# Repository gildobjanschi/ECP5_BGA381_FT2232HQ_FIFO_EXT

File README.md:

# Extension board for ECP5_BGA381_FT2232HQ_FIFO
This is an extension board for the [ECP5_BGA381_FT2232HQ_FIFO](https://github.com/gildobjanschi/ECP5_BGA381_FT2232HQ_FIFO) board. It is used to validate the main board design and to provide audio output connectors for I2S (HDMI) and SPDIF (Coaxial).

## Software
The bringup software that supports this board is located in the main board [ECP5_BGA381_FT2232HQ_FIFO](https://github.com/gildobjanschi/ECP5_BGA381_FT2232HQ_FIFO/tree/main/hdl_loopback) project. The [host software](https://github.com/gildobjanschi/ECP5_BGA381_FT2232HQ_FIFO/tree/main/host_loopback) is a simple application for testing the FIFO interface.

## Project Status
The board has been submitted to manufacturing to PCBWay.

[Schematic PDF](https://github.com/gildobjanschi/ECP5_BGA381_FT2232HQ_FIFO_EXT/blob/main/kicad/ECP5_Ext.pdf)

## How To setup KiCAD
Checkout the KiCAD project and open it. In the Configure Paths dialog add: Name: ECP5_BGA381_FT2232HQ_FIFO_EXT and Path: "The full path to the GitHub directory"/GitHub/ECP5_BGA381_FT2232HQ_FIFO_EXT

In the Manage Symbol Libraries click the Project Specific Libraries tab and add: Name: ECP5_BGA381_FT2232HQ_FIFO_EXT and Library Path: ${ECP5_BGA381_FT2232HQ_FIFO_EXT}/symbols/Symbols.kicad_sym

In the Manage Footprint Libraries click the Project Specific Libraries tab and add: Name: ECP5_BGA381_FT2232HQ_FIFO_EXT and Library Path: ${ECP5_BGA381_FT2232HQ_FIFO_EXT}/footprints/Footprints.pretty

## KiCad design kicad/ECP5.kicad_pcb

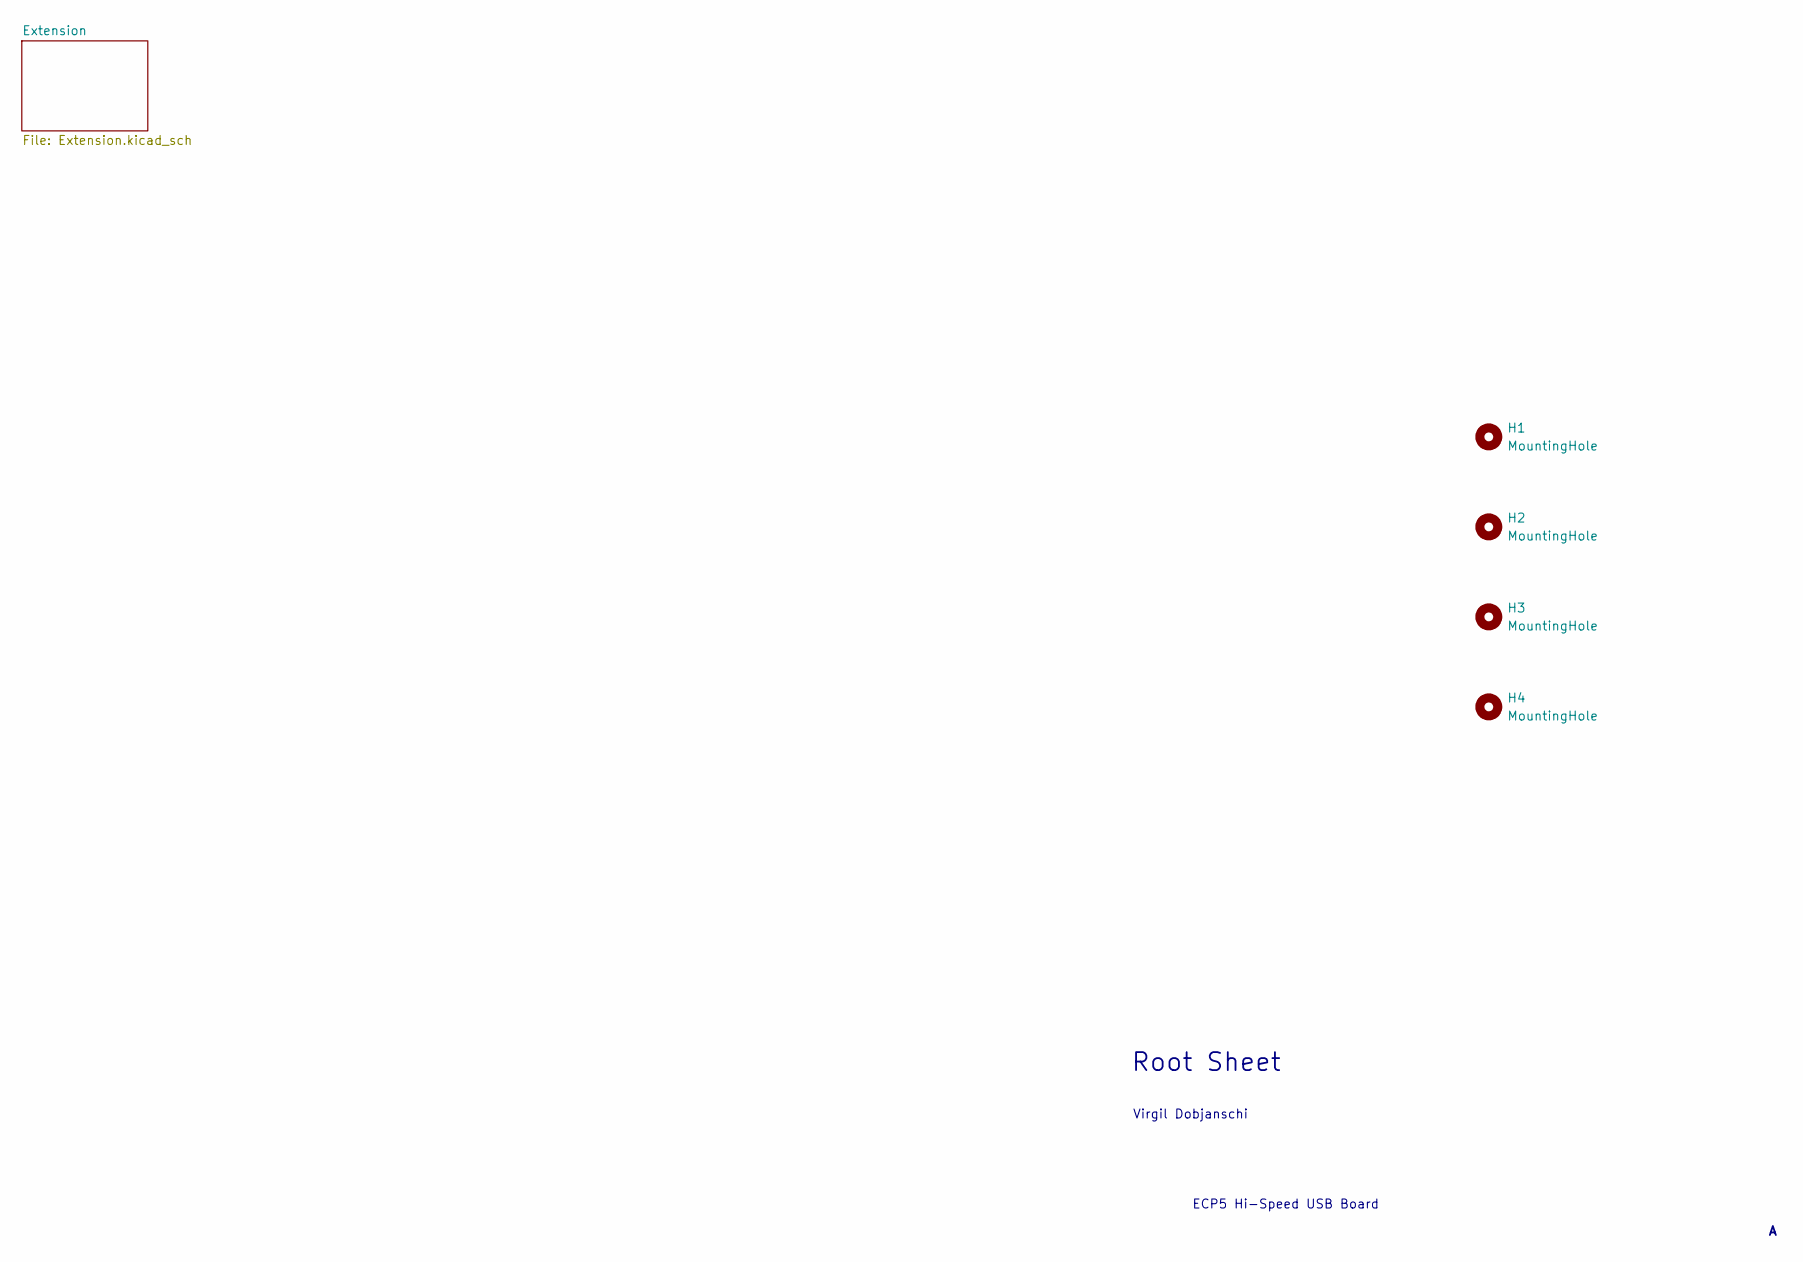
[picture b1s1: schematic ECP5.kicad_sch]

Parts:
H1, H2, H3, H4: MountingHole; MountingHole_3.2mm_M3

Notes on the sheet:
ECP5 Hi-Speed USB Board
Root Sheet
Virgil Dobjanschi

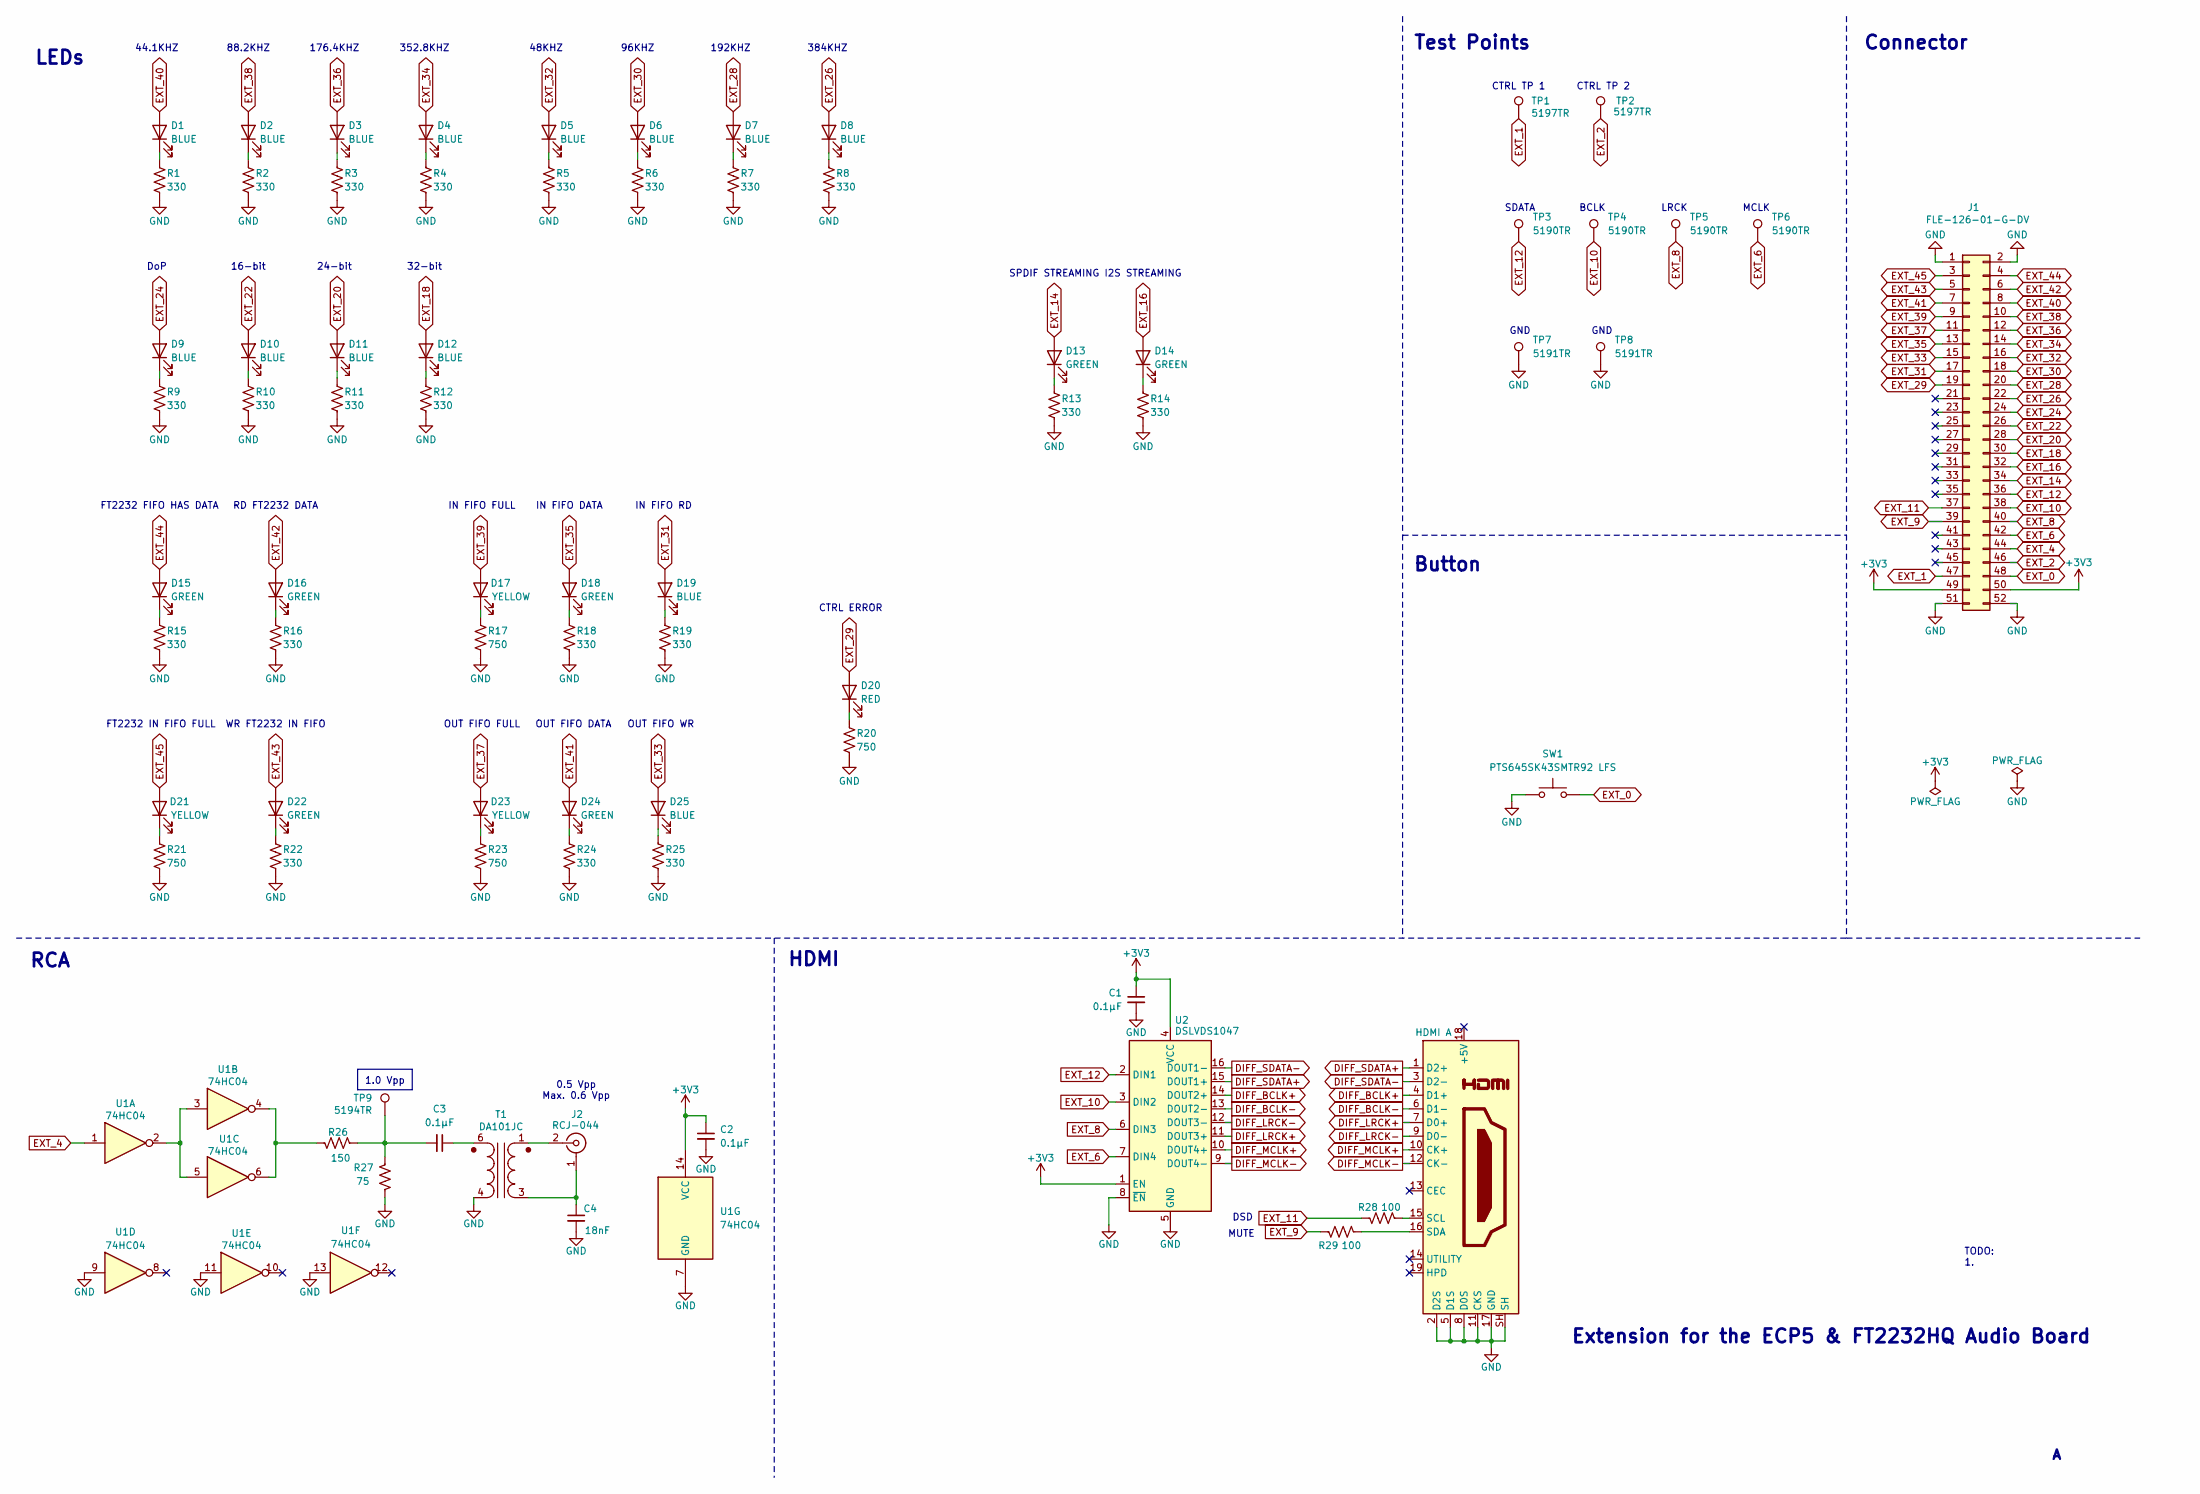
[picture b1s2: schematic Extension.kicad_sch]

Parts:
C1, C2, C3: 0.1µF; C_0603_1608Metric; MPN CL10B104KB8NNNC
C4: 18nF; C_0603_1608Metric; MPN CC0603KRX7R9BB183
D1, D2, D3, D4, D5, D6, D7, D8, D9, D10, D11, D12, D19, D25: BLUE; LED_0603_1608Metric; MPN APT1608LVBC/D
D13, D14, D15, D16, D18, D22, D24: GREEN; LED_0603_1608Metric; MPN APT1608LZGCK
D17, D21, D23: YELLOW; LED_0603_1608Metric; MPN APT1608LSYCK/J3-PRV
D20: RED; LED_0603_1608Metric; MPN APT1608LSECK/J3-PRV
J1: FLE-126-01-G-DV; SAMTEC_FLE-126-01-G-DV; MPN FLE-126-01-G-DV
J2: RCJ-044; CUI_RCJ-042; MPN RCJ-044
J3: HDMI A; AMPHENOL_10029449-001RLF; MPN 10029449-001RLF
R1, R2, R3, R4, R5, R6, R7, R8, R9, R10, R11, R12, R13, R14, R15, R16, R18, R19, R22, R24, R25: 330; R_0603_1608Metric; MPN ERJ-3EKF3300V
R17, R20, R21, R23: 750; R_0603_1608Metric; MPN ERJ-3EKF7500V
R26: 150; R_0603_1608Metric; MPN ERJ-3EKF1500V
R27: 75; R_0603_1608Metric; MPN ERJ-3EKF75R0V
R28, R29: 100; R_0603_1608Metric; MPN ERJ-3EKF1000V
SW1: PTS645SK43SMTR92 LFS; SW_SPST_PTS645; MPN PTS645SK43SMTR92 LFS
T1: DA101JC; DA101J_MUR; MPN DA101JC
TP1, TP2: 5197TR; KEYSTONE_5197TR; MPN 5197TR
TP3, TP4, TP5, TP6: 5190TR; KEYSTONE_5197TR; MPN 5190TR
TP7, TP8: 5191TR; KEYSTONE_5197TR; MPN 5191TR
TP9: 5194TR; KEYSTONE_5197TR; MPN 5194TR
U1: 74HC04; TSSOP-14_4.4x5mm_P0.65mm; MPN SN74HC04PWR
U2: DSLVDS1047; TSSOP-16-1EP_4.4x5mm_P0.65mm; MPN DSLVDS1047PWR

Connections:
+3V3: C1.1, C2.1, J1.49, J1.50, U1.14 (VCC), U2.1 (EN), U2.4 (VCC)
DIFF_BCLK+: J3.4 (D1+), U2.14 (DOUT2+)
DIFF_BCLK-: J3.6 (D1-), U2.13 (DOUT2-)
DIFF_LRCK+: J3.7 (D0+), U2.11 (DOUT3+)
DIFF_LRCK-: J3.9 (D0-), U2.12 (DOUT3-)
DIFF_MCLK+: J3.10 (CK+), U2.10 (DOUT4+)
DIFF_MCLK-: J3.12 (CK-), U2.9 (DOUT4-)
DIFF_SDATA+: J3.1 (D2+), U2.15 (DOUT1+)
DIFF_SDATA-: J3.3 (D2-), U2.16 (DOUT1-)
EXT_0: J1.48, SW1.2
EXT_1: J1.47, TP1.1
EXT_2: J1.46, TP2.1
EXT_4: J1.44, U1.1
EXT_6: J1.42, TP6.1, U2.7 (DIN4)
EXT_8: J1.40, TP5.1, U2.6 (DIN3)
EXT_9: J1.39, R29.2
EXT_10: J1.38, TP4.1, U2.3 (DIN2)
EXT_11: J1.37, R28.2
EXT_12: J1.36, TP3.1, U2.2 (DIN1)
EXT_14: D13.2 (A), J1.34
EXT_16: D14.2 (A), J1.32
EXT_18: D12.2 (A), J1.30
EXT_20: D11.2 (A), J1.28
EXT_22: D10.2 (A), J1.26
EXT_24: D9.2 (A), J1.24
EXT_26: D8.2 (A), J1.22
EXT_28: D7.2 (A), J1.20
EXT_29: D20.2 (A), J1.19
EXT_30: D6.2 (A), J1.18
EXT_31: D19.2 (A), J1.17
EXT_32: D5.2 (A), J1.16
EXT_33: D25.2 (A), J1.15
EXT_34: D4.2 (A), J1.14
EXT_35: D18.2 (A), J1.13
EXT_36: D3.2 (A), J1.12
EXT_37: D23.2 (A), J1.11
EXT_38: D2.2 (A), J1.10
EXT_39: D17.2 (A), J1.9
EXT_40: D1.2 (A), J1.8
EXT_41: D24.2 (A), J1.7
EXT_42: D16.2 (A), J1.6
EXT_43: D22.2 (A), J1.5
EXT_44: D15.2 (A), J1.4
EXT_45: D21.2 (A), J1.3
GND: C1.2, C2.2, C4.2, J1.1, J1.2, J1.51, J1.52, J3.2 (D2S), J3.5 (D1S), J3.8 (D0S), J3.11 (CKS), J3.17 (GND), J3.SH, R1.2, R2.2, R3.2, R4.2, R5.2, R6.2, R7.2, R8.2, R9.2, R10.2, R11.2, R12.2, R13.2, R14.2, R15.2, R16.2, R17.2, R18.2, R19.2, R20.2, R21.2, R22.2, R23.2, R24.2, R25.2, R27.2, SW1.1, T1.4 (SA), TP7.1, TP8.1, U1.7 (GND), U1.9, U1.11, U1.13, U2.5 (GND), U2.8 (~EN)
unnamed: C3.2, R26.1, R27.1, TP9.1
unnamed: D1.1 (K), R1.1
unnamed: D2.1 (K), R2.1
unnamed: D3.1 (K), R3.1
unnamed: D4.1 (K), R4.1
unnamed: D5.1 (K), R5.1
unnamed: D6.1 (K), R6.1
unnamed: D7.1 (K), R7.1
unnamed: D8.1 (K), R8.1
unnamed: D9.1 (K), R9.1
unnamed: D10.1 (K), R10.1
unnamed: D11.1 (K), R11.1
unnamed: D12.1 (K), R12.1
unnamed: D13.1 (K), R13.1
unnamed: D14.1 (K), R14.1
unnamed: D15.1 (K), R15.1
unnamed: D16.1 (K), R16.1
unnamed: D17.1 (K), R17.1
unnamed: D18.1 (K), R18.1
unnamed: D19.1 (K), R19.1
unnamed: D20.1 (K), R20.1
unnamed: D21.1 (K), R21.1
unnamed: D22.1 (K), R22.1
unnamed: D23.1 (K), R23.1
unnamed: D24.1 (K), R24.1
unnamed: D25.1 (K), R25.1
unnamed: C4.1, J2.1 (Ext), T1.3 (AB)
unnamed: J2.2 (In), T1.1 (AA)
unnamed: J3.15 (SCL), R28.1
unnamed: J3.16 (SDA), R29.1
unnamed: R26.2, U1.4, U1.6
unnamed: C3.1, T1.6 (SB)
unnamed: U1.2, U1.3, U1.5

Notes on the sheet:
24-bit
RCA
48KHZ
HDMI
IN FIFO DATA
SDATA
BCLK
DSD
192KHZ
FT2232 FIFO HAS DATA
CTRL TP 2
TODO: 1.
352.8KHZ
CTRL TP 1
Connector
RD FT2232 DATA
Button
IN FIFO RD
Test Points
GND
1.0 Vpp
OUT FIFO DATA
OUT FIFO WR
OUT FIFO FULL
44.1KHZ
176.4KHZ
96KHZ
FT2232 IN FIFO FULL
0.5 Vpp Max. 0.6 Vpp
CTRL ERROR
MCLK
Extension for the ECP5 & FT2232HQ Audio Board
SPDIF STREAMING
16-bit
WR FT2232 IN FIFO
LRCK
32-bit
384KHZ
I2S STREAMING
88.2KHZ

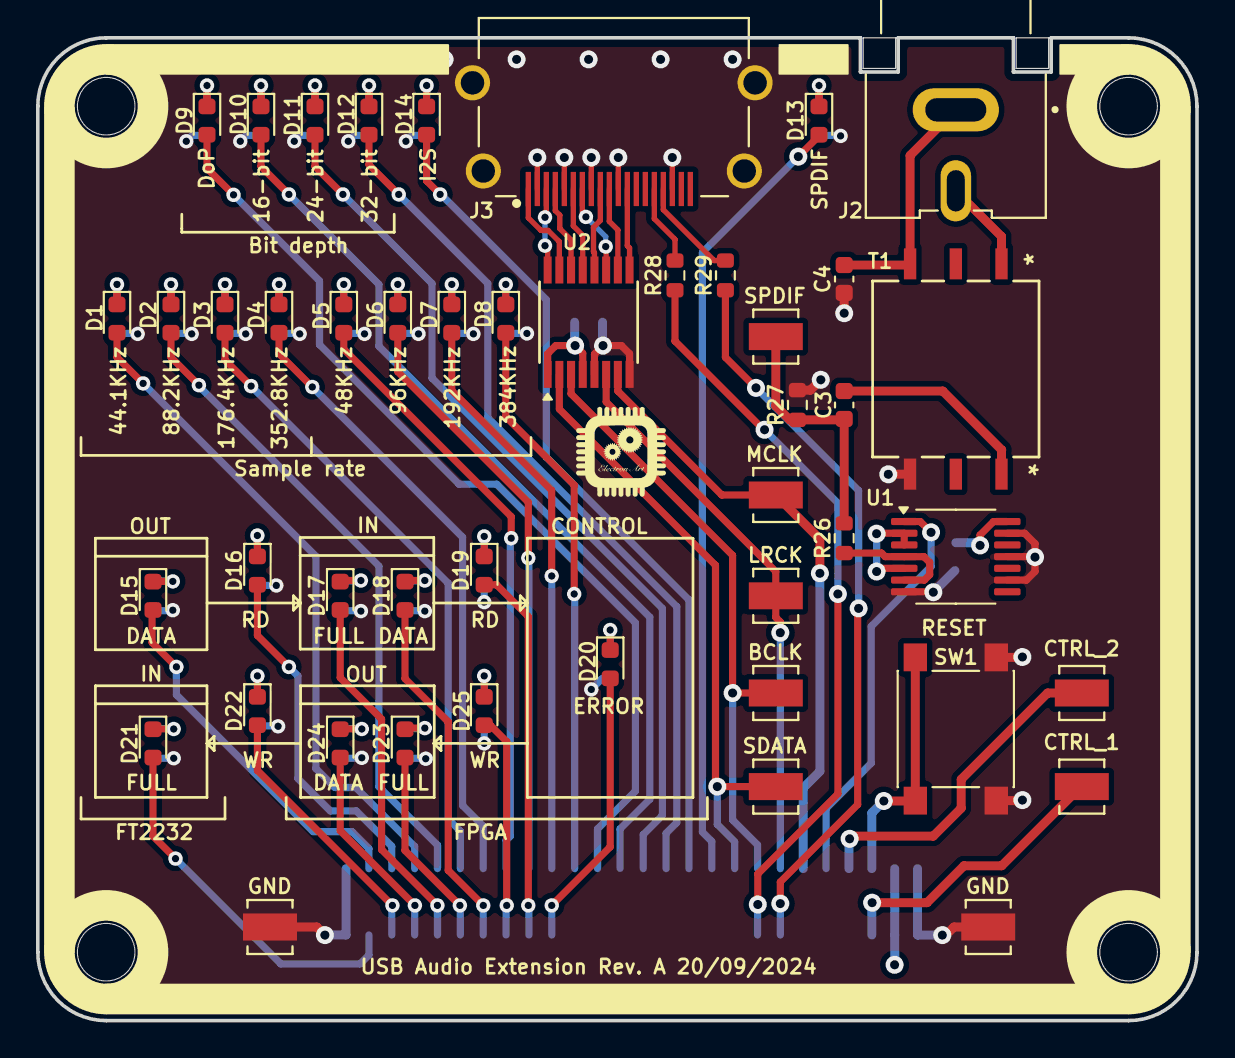
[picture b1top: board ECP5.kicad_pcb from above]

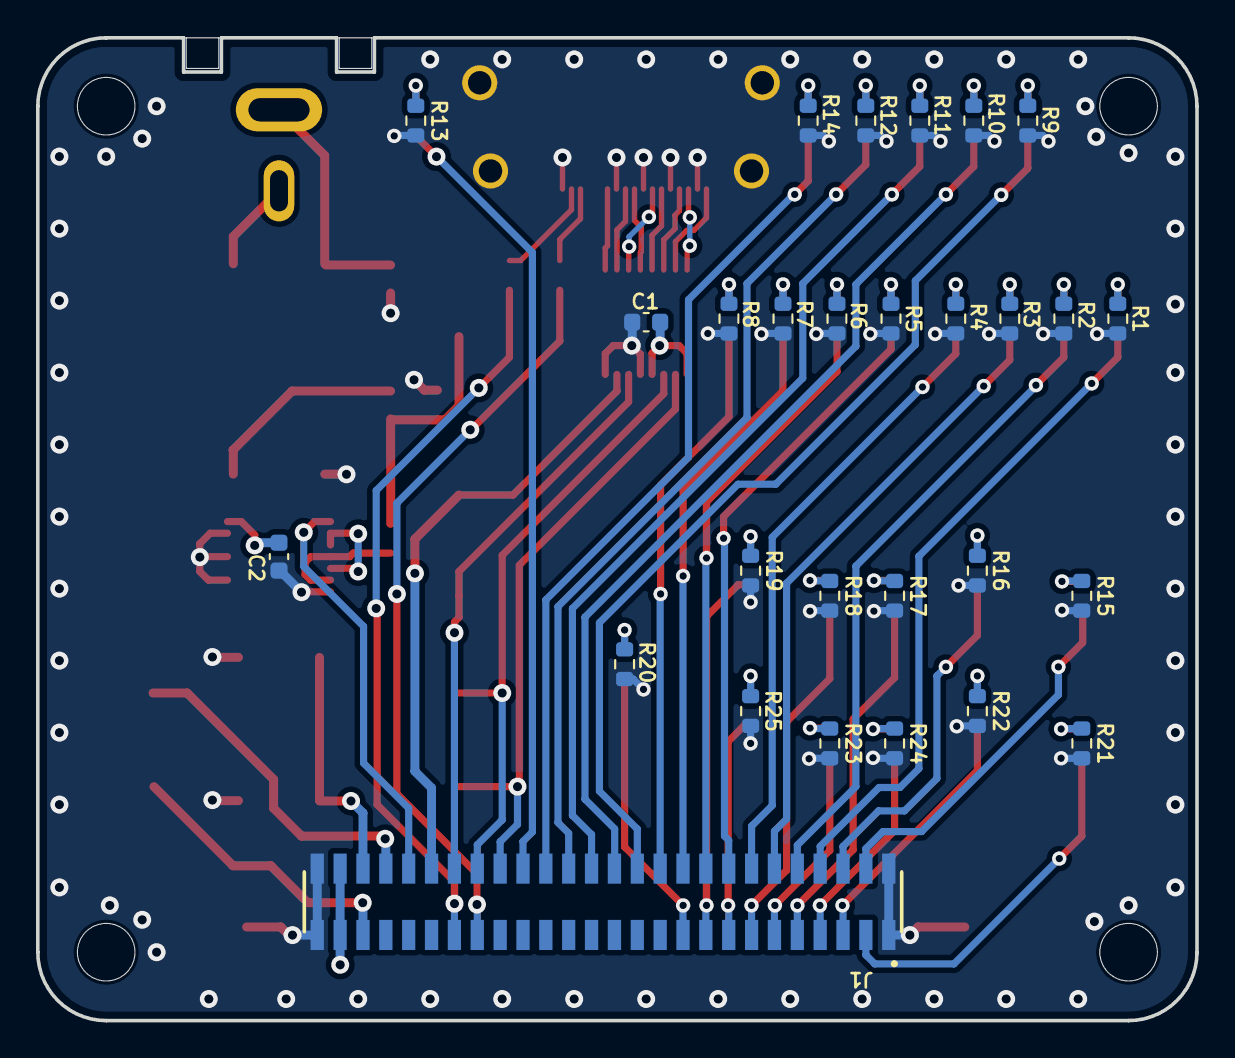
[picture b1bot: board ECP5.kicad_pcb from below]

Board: 4 copper layers, 64.4 x 54.6 mm, 78 parts (28 on the bottom side), 78 nets.

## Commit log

2024-09-06 Changed the name of the project path to ECP5_BGA381_FT2232HQ_FIFO_EXT
2024-09-18 First pass at arranging components
2024-09-18 Updated the BOM
2024-09-19 Removed unused symbols and footprints
2024-09-19 First routing
2024-09-19 Added schematics pdf
2024-09-19 Updated PCB
2024-10-18 Added measurements
